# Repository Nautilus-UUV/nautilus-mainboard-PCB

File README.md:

# Nautilus Mainboard PCB
## Overview
This PCB houses an [STM32H7B0RBT6](https://www.st.com/resource/en/datasheet/stm32h7b0ab.pdf) together with a [CM4](https://pip-assets.raspberrypi.com/categories/634-raspberry-pi-compute-module-4/documents/RP-008168-DS-1-cm4-datasheet.pdf?disposition=inline). The STM32 is primarily used for communication over CanOpen with all the other PCBs while the CM4 is intended to run higher level calculations and then being shut off again. The CM4 is connected to an SSD. The CM4 and STM are connected over Uart (RX, TX) closely for communication and there is an integrated option for the STM to power off and on the CM4. (Currently the CM4's RUN_PG is connected to the STM32's pin number 10.) The STM has a crystal while the CM4 currently does not have one since it was not requested.

Additionally the mainboard provides two IMUs ([BMI088](https://www.bosch-sensortec.com/media/boschsensortec/downloads/datasheets/bst-bmi088-ds001.pdf)) that can be accessed over SPI on the STM32.

The Power supply is primarily provided by the UUV's battery lines (5V, 3.3V and GND) but the board also accepts USB-C 2.0 for both data and power inputs (only powering the CM4 and nothing else) or the 3.3V Power supply over the STM programmer pins. (only powers the STM32) The power logic is achieved using three [TPS2121RUXT](https://www.ti.com/lit/ds/symlink/tps2120.pdf?ts=1761678178328) (one for 5V, one for 3.3V and one for the GPIO reference of both microcontrollers.)

> [!CAUTION]
> The Power supply logic can be bypassed completely by soldering on 0 Ohm resistors on the designated spots for both 5V and 3.3V, but this still needs to be worked on.
> Also Im not 100% sure if the 0.8A provided by a laptop is sufficient for the CM4, it is possible that a direct battery connection is needed when programming it on the mainboard. For convenience please use the IO board for coding.

### WIP

Differential pairs have been routed and matched in length but the trace widths still need to be recalculated and adjusted.

The whole board works on 2 layers with an additional ground layer in mind (until now 1 free layer)

If someone wants to write a better README, feel free to do so, I'd appreciate it.

This PCB has not yet been reviewed or tested in a physical form.

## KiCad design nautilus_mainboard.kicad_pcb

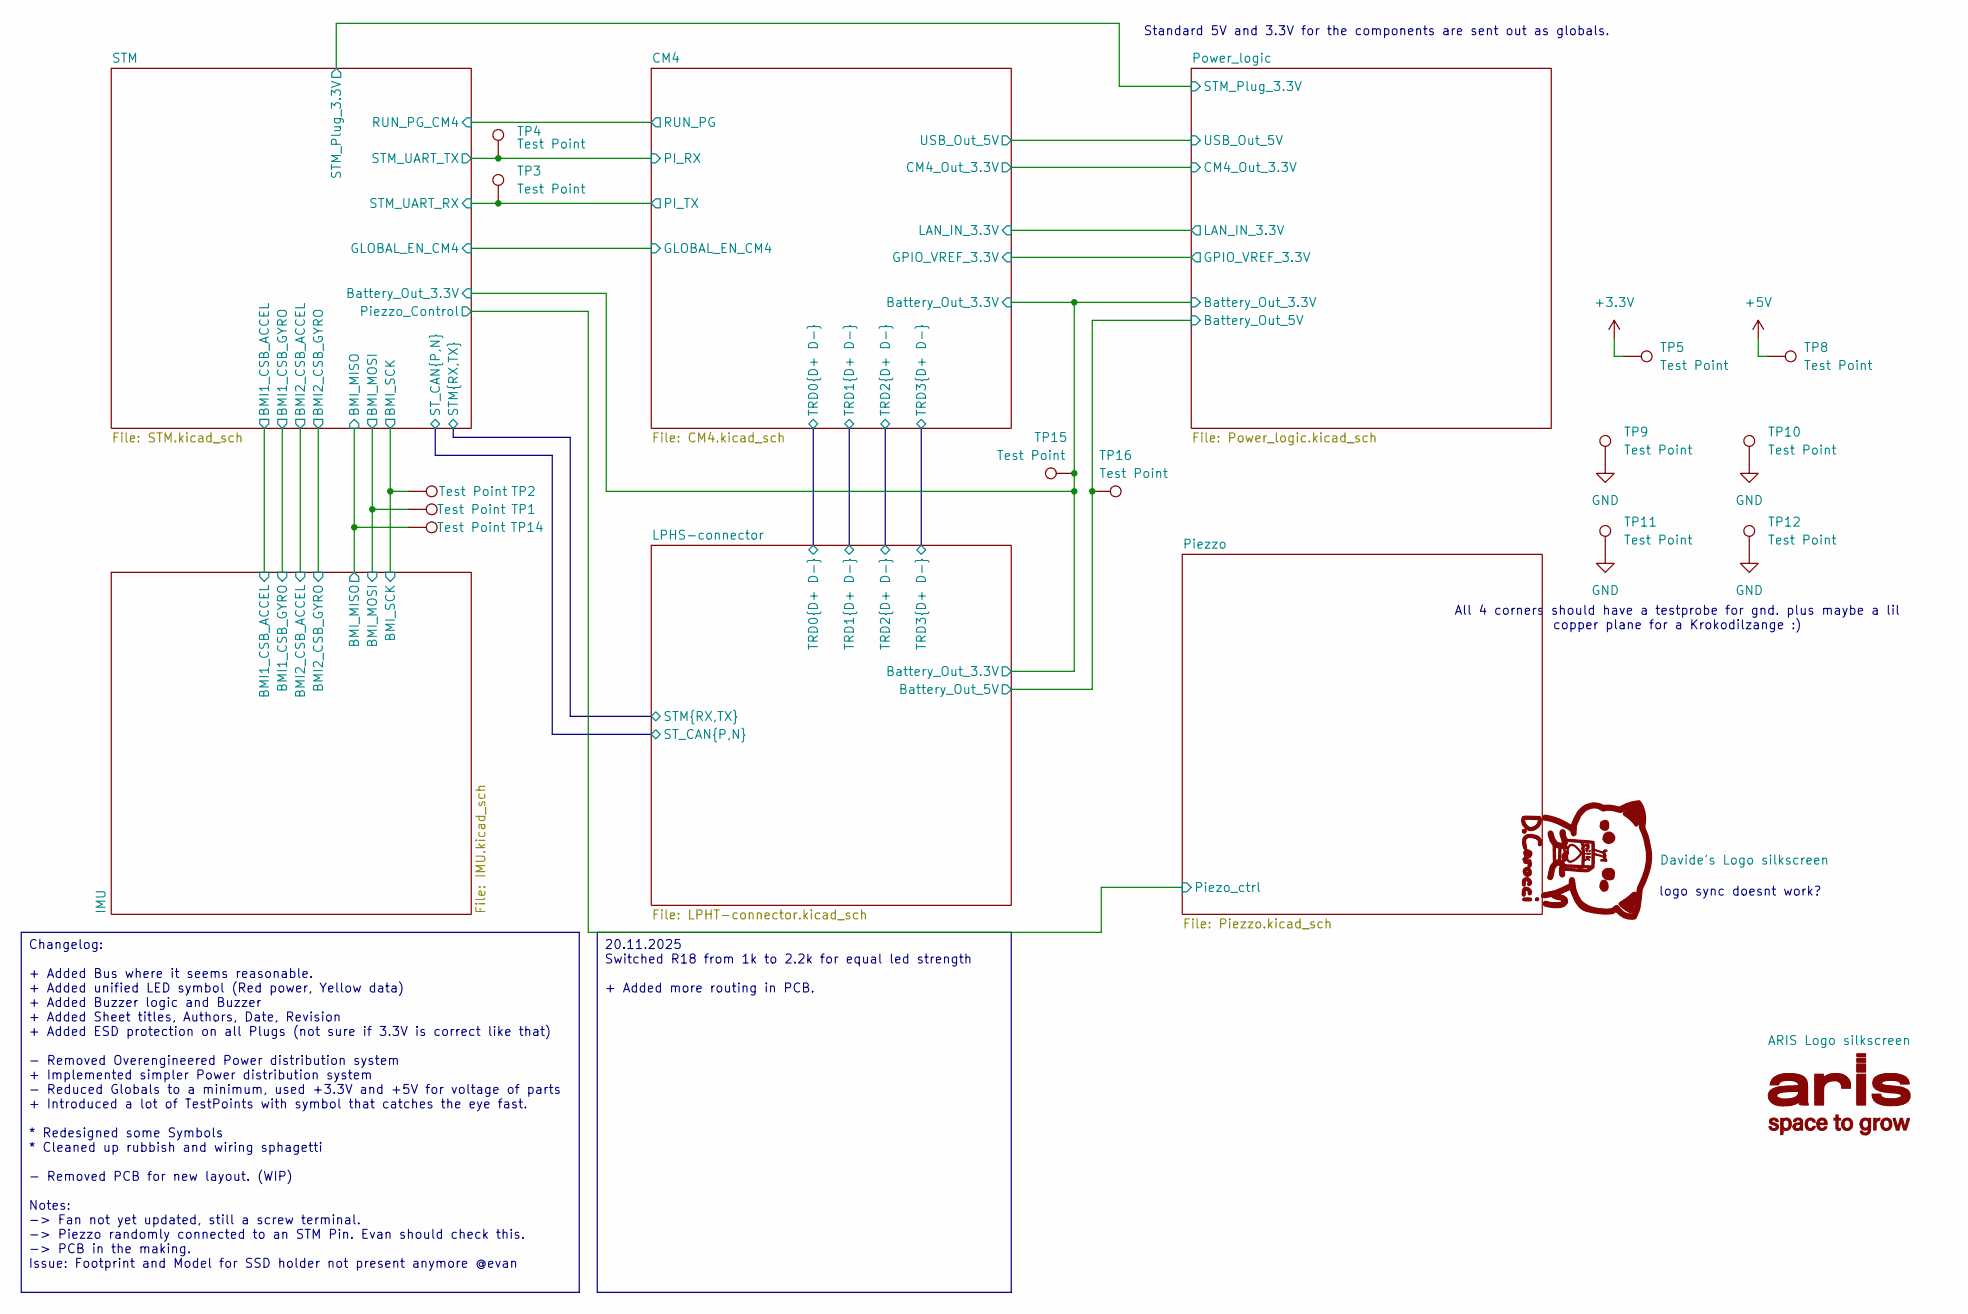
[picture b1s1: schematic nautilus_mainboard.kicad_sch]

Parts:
TP1, TP2, TP3, TP4, TP5, TP8, TP9, TP10, TP11, TP12, TP14, TP15, TP16: Test Point; TestPoint_Pad_D1.5mm

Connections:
+3.3V: TP5.1; also elsewhere on the board
+5V: TP8.1; also elsewhere on the board
/CM4/Battery_Out_3.3V: TP15.1; also elsewhere on the board
/IMU/BMI_MISO: TP14.1; also elsewhere on the board
/IMU/BMI_MOSI: TP1.1; also elsewhere on the board
/IMU/BMI_SCK: TP2.1; also elsewhere on the board
/LPHS-connector/Battery_Out_5V: TP16.1; also elsewhere on the board
/STM/PinoutSTM/USART2_RX: TP3.1; also elsewhere on the board
/STM/PinoutSTM/USART2_TX: TP4.1; also elsewhere on the board
GND: TP9.1, TP10.1, TP11.1, TP12.1; also elsewhere on the board

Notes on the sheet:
Standard 5V and 3.3V for the components are sent out as globals.
All 4 corners should have a testprobe for gnd. plus maybe a lil copper plane for a Krokodilzange :)
logo sync doesnt work?
20.11.2025 Switched R18 from 1k to 2.2k for equal led strength + Added more routing in PCB.
Changelog: + Added Bus where it seems reasonable. + Added unified LED symbol (Red power, Yellow data) + Added Buzzer logic and Buzzer + Added Sheet titles, Authors, Date, Revision + Added ESD protection on all Plugs (not sure if 3.3V is correct like that) - Removed Overengineered Power distribution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

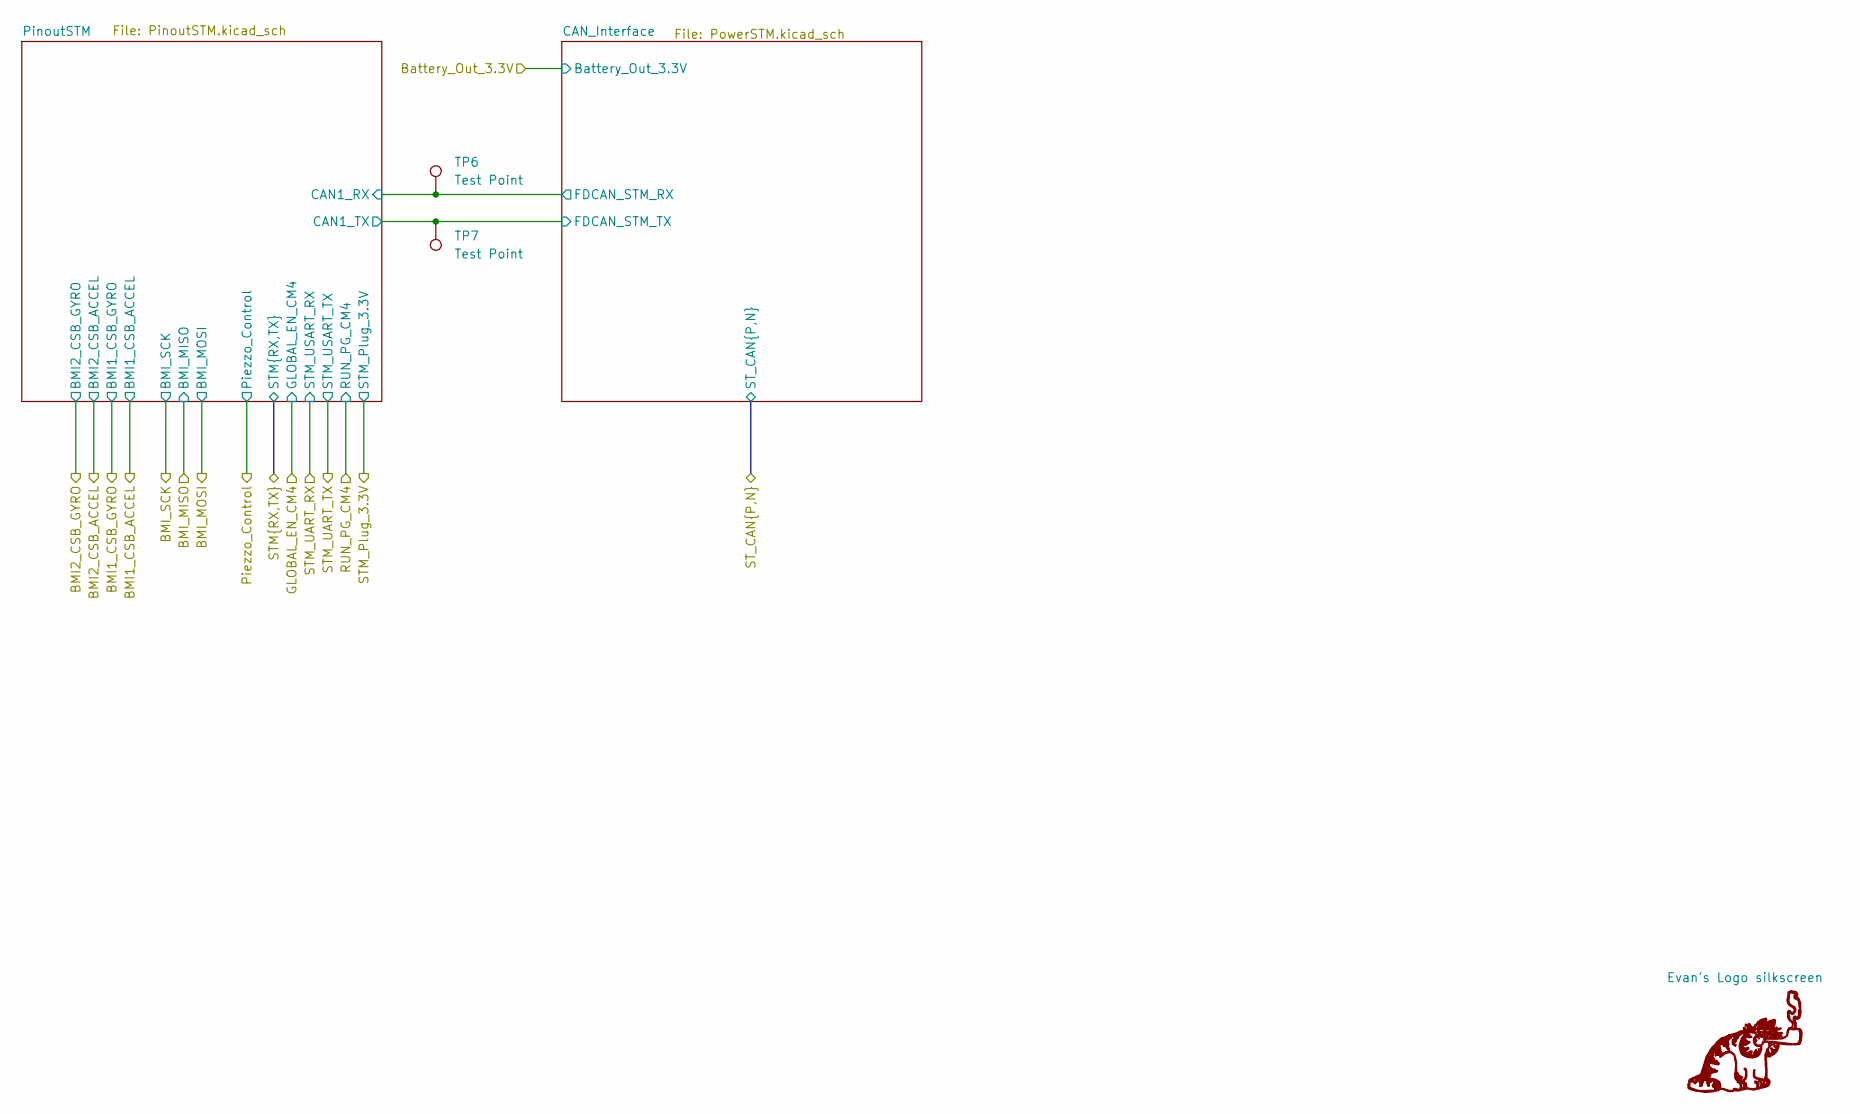
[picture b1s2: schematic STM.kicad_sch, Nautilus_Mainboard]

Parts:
TP6, TP7: Test Point; TestPoint_Pad_D1.5mm

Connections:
/STM/PinoutSTM/CAN1_RX: TP6.1; also elsewhere on the board
/STM/PinoutSTM/CAN1_TX: TP7.1; also elsewhere on the board

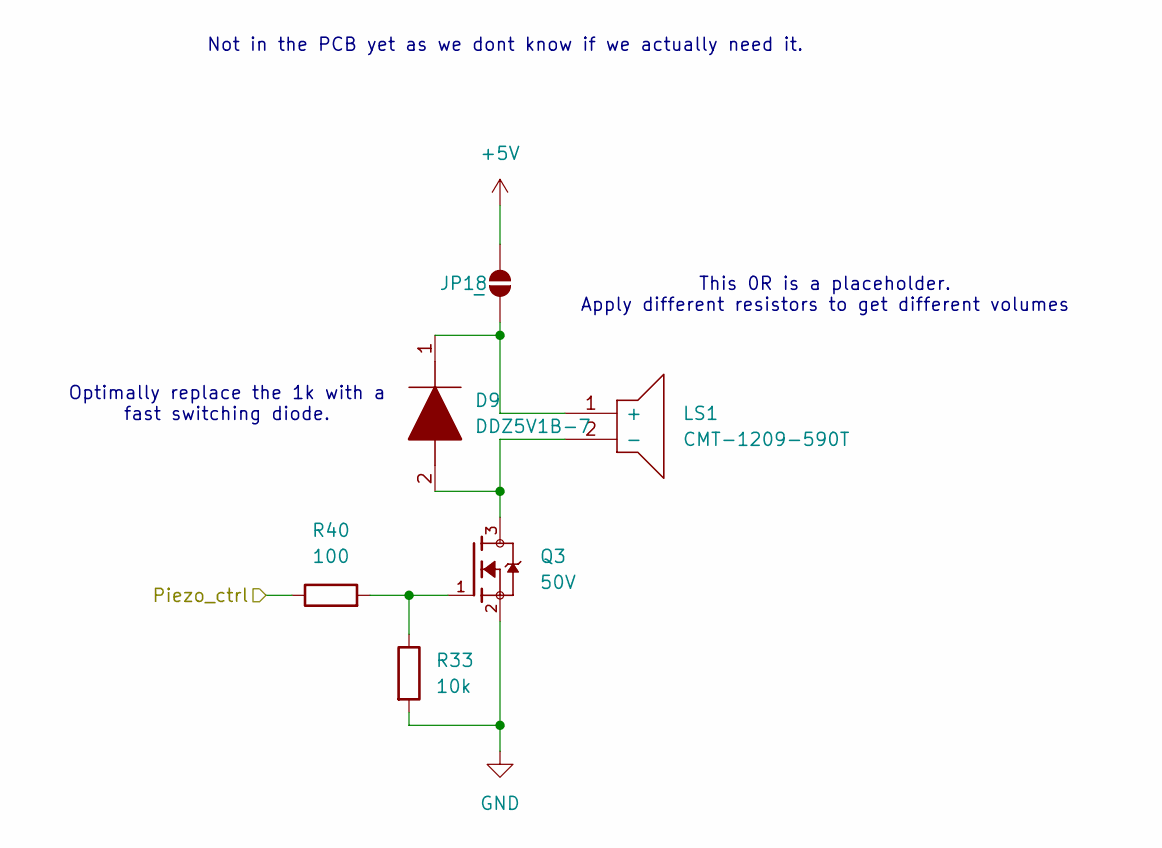
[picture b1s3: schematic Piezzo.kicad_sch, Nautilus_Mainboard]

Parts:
D9: DDZ5V1B-7; SOD3716X145N; Mouser Part Number 621-DDZ5V1B-7
JP18: -; SolderJumper-2_P1.3mm_Open_RoundedPad1.0x1.5mm
LS1: Piezo Buzzers & Audio Indicators 12mmx9mm deep Ma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; CMT1209590T; Mouser Part Number 179-CMT-1209-590T
Q3: 50V; onsemi_Mosfet_BSS138; PARTREV 30 Jan 2018
R33: 10k; R_0603_1608Metric; Tolerance 1 %; MPN 560112116005; LCSC CXXXXX
R40: 100; R_0402_1005Metric; Tolerance 1%; MPN ERJ-2RKF1000X; LCSC C413063

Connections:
+5V: JP18.2 (B); also elsewhere on the board
/Piezzo/Piezo_ctrl: R40.1; also elsewhere on the board
GND: Q3.2, R33.2; also elsewhere on the board
unnamed: D9.1, JP18.1 (A), LS1.1 (+)
unnamed: D9.2, LS1.2 (-), Q3.3
unnamed: Q3.1, R33.1, R40.2

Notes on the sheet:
Optimally replace the 1k with a fast switching diode.
This 0R is a placeholder. Apply different resistors to get different volumes
Not in the PCB yet as we dont know if we actually need it.

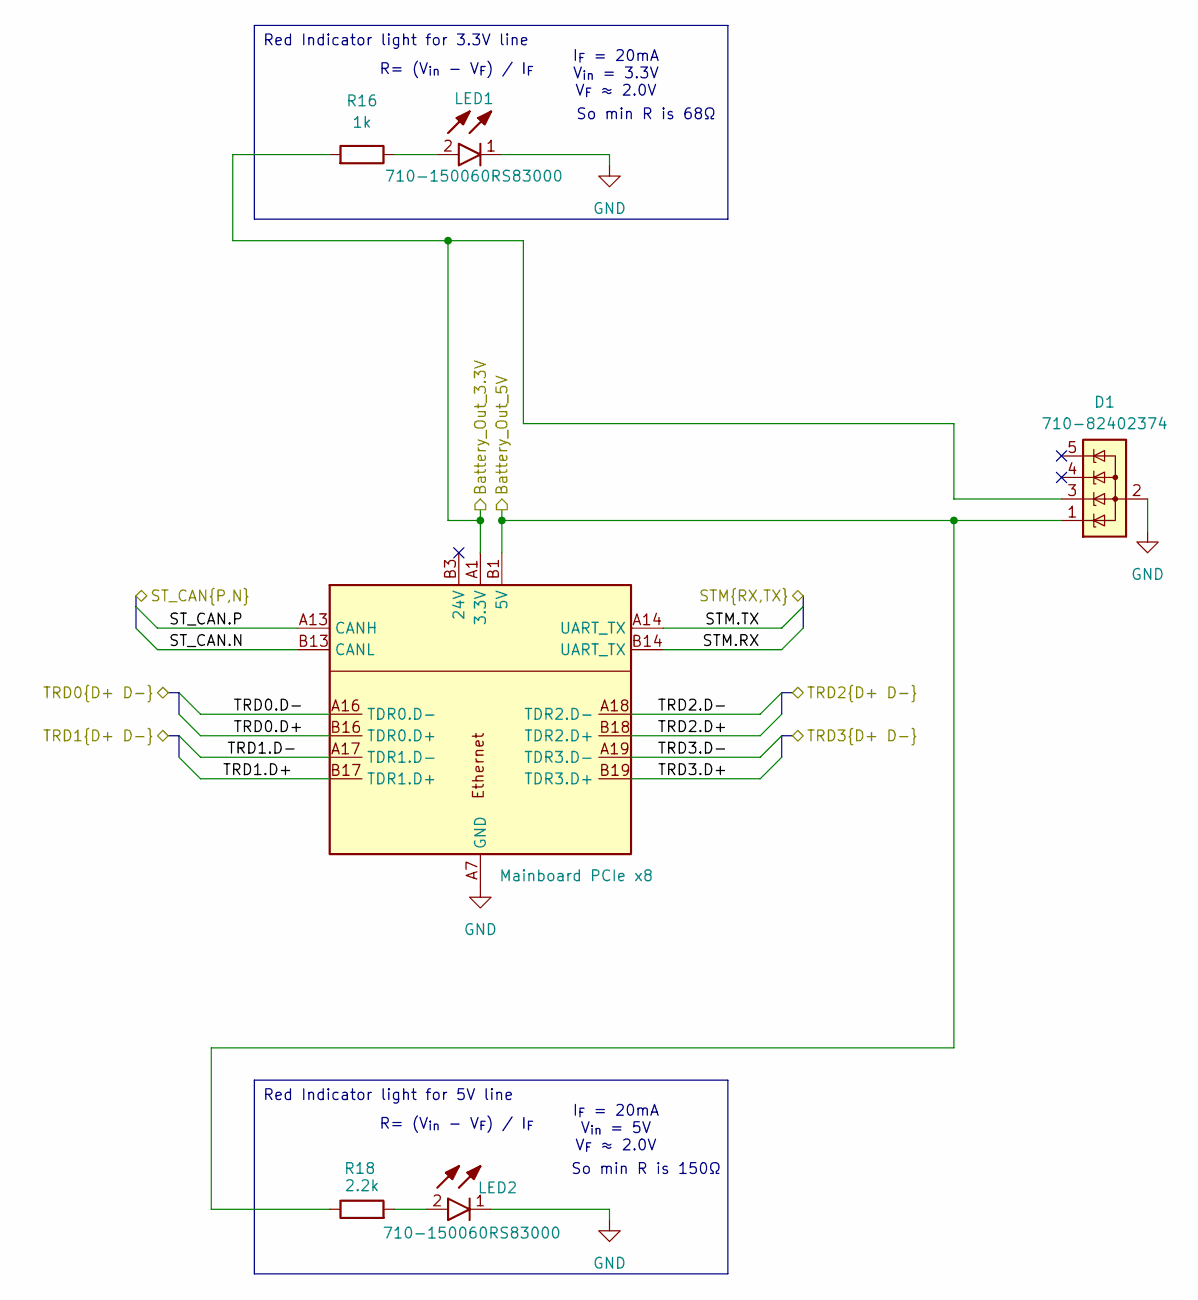
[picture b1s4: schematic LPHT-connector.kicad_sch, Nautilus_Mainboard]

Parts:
D1: 710-82402374; SOT-23-5; MPN 710-82402374
J2: Mainboard PCIe x8; BUS_PCIexpress_x8
LED1, LED2: 710-150060RS83000; Wuerth_LED_150060RS83000; Manufacturer_Part_Number 150060RS83000
R16: 1k; R_0603_1608Metric; Tolerance 1 %; MPN 560112116014; LCSC CXXXXX
R18: 2.2k; R_0603_1608Metric; Tolerance 1 %; MPN 560112116098; LCSC CXXXXX

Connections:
24V: J2.A3 (24V), J2.A4 (24V), J2.A5 (24V), J2.A6 (24V), J2.B4 (24V), J2.B5 (24V), J2.B6 (24V)
/CM4/Battery_Out_3.3V: D1.3 (K), J2.A1 (3.3V), J2.A2 (3.3V), R16.2; also elsewhere on the board
/CM4/TRD0.D+: J2.B16 (TDR0.D+); also elsewhere on the board
/CM4/TRD0.D-: J2.A16 (TDR0.D-); also elsewhere on the board
/CM4/TRD1.D+: J2.B17 (TDR1.D+); also elsewhere on the board
/CM4/TRD1.D-: J2.A17 (TDR1.D-); also elsewhere on the board
/CM4/TRD2.D+: J2.B18 (TDR2.D+); also elsewhere on the board
/CM4/TRD2.D-: J2.A18 (TDR2.D-); also elsewhere on the board
/CM4/TRD3.D+: J2.B19 (TDR3.D+); also elsewhere on the board
/CM4/TRD3.D-: J2.A19 (TDR3.D-); also elsewhere on the board
/LPHS-connector/Battery_Out_5V: D1.1 (K), J2.B1 (5V), R18.1; also elsewhere on the board
/LPHS-connector/STM.RX: J2.B14 (UART_TX); also elsewhere on the board
/LPHS-connector/STM.TX: J2.A14 (UART_TX); also elsewhere on the board
/LPHS-connector/ST_CAN.N: J2.B13 (CANL); also elsewhere on the board
/LPHS-connector/ST_CAN.P: J2.A13 (CANH); also elsewhere on the board
GND: D1.2 (A), J2.A7 (GND), J2.A8 (GND), J2.A9 (GND), J2.A10 (GND), J2.A11 (GND), J2.A12 (GND), J2.A21 (GND), J2.A24 (GND), J2.A27 (GND), J2.A29 (GND), J2.B7 (GND), J2.B8 (GND), J2.B9 (GND), J2.B10 (GND), J2.B11 (GND), J2.B12 (GND), LED1.1 (K), LED2.1 (K); also elsewhere on the board
unnamed: LED1.2 (A), R16.1
unnamed: LED2.2 (A), R18.2

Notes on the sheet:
I_{F} = 20mA V_{in} = 5V V_{F} ≈ 2.0V
R= (V_{in} - V_{F}) / I_{F}
So min R is 150Ω
So min R is 68Ω
I_{F} = 20mA V_{in} = 3.3V V_{F} ≈ 2.0V
Red Indicator light for 3.3V line
Red Indicator light for 5V line

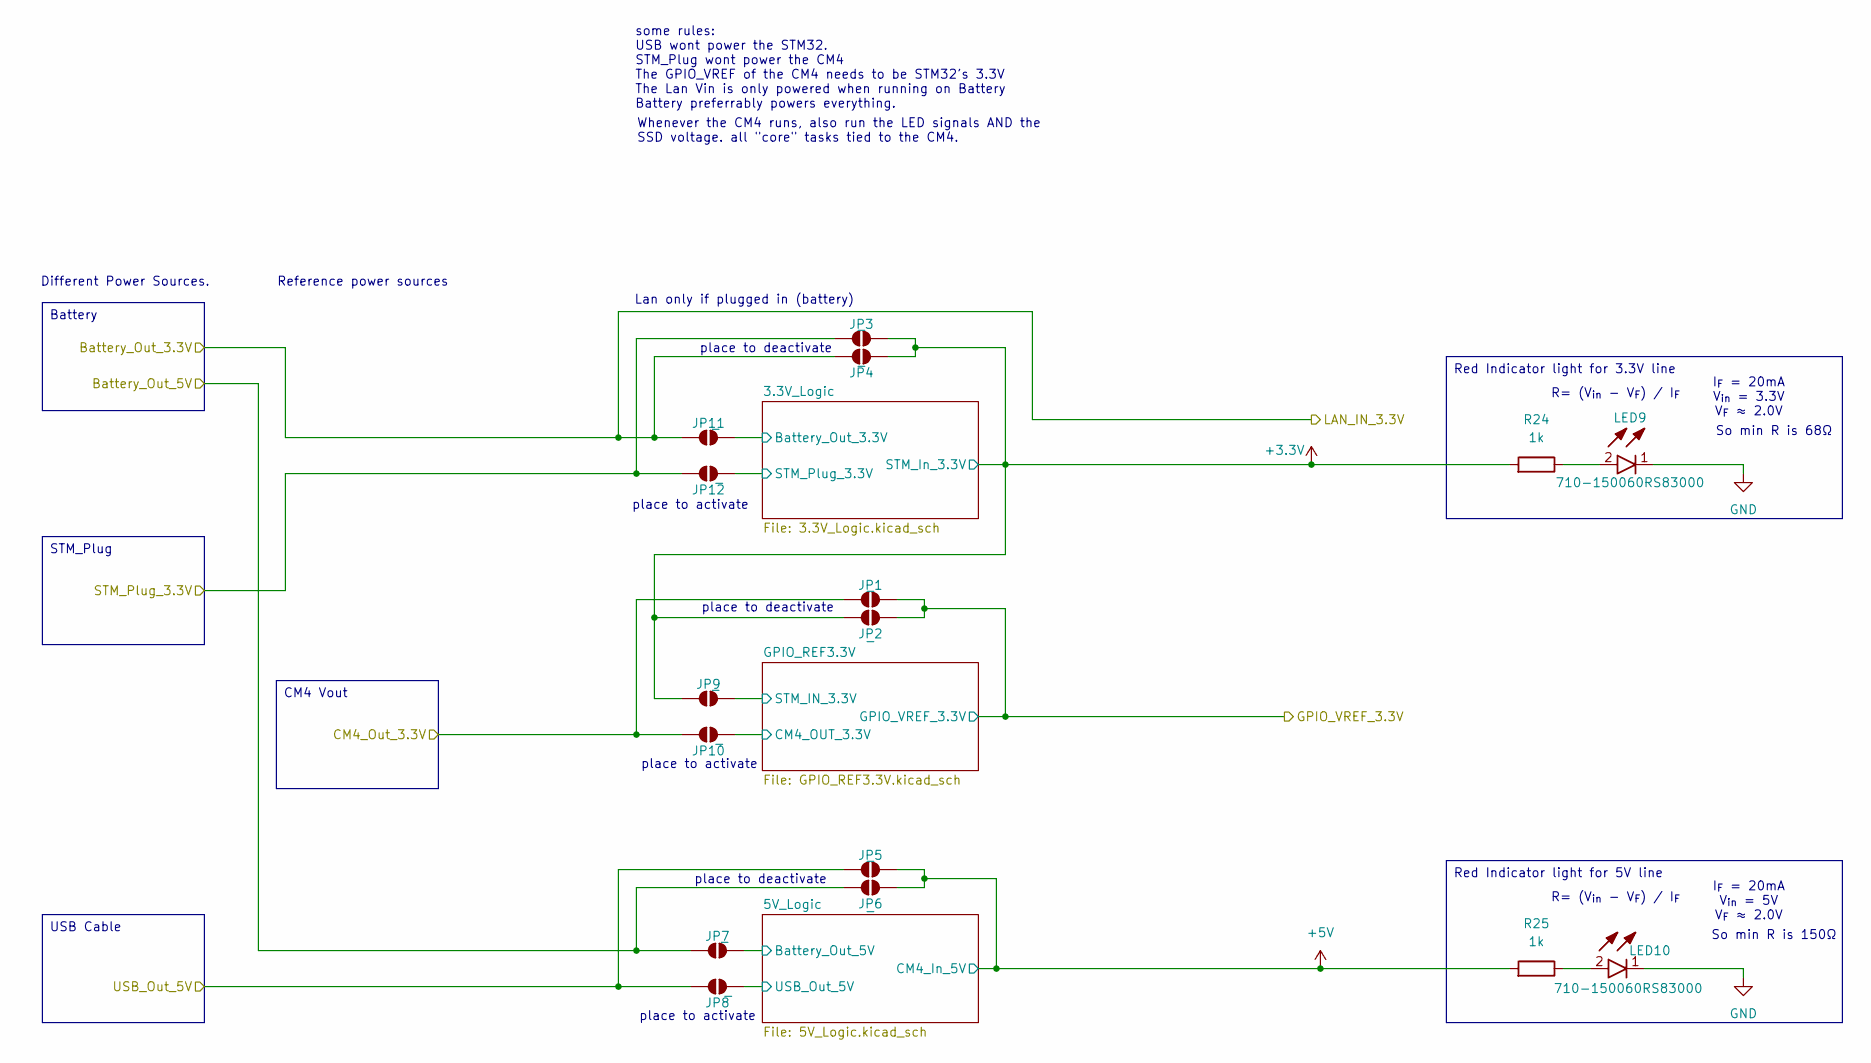
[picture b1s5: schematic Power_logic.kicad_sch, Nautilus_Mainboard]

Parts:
JP1, JP2, JP3, JP4, JP5, JP6, JP7, JP8, JP9, JP10, JP11, JP12: -; SolderJumper-2_P1.3mm_Open_RoundedPad1.0x1.5mm
LED9, LED10: 710-150060RS83000; Wuerth_LED_150060RS83000; Manufacturer_Part_Number 150060RS83000
R24, R25: 1k; R_0603_1608Metric; Tolerance 1 %; MPN 560112116014; LCSC CXXXXX

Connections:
+3.3V: JP2.1 (A), JP3.2 (B), JP4.2 (B), JP9.1 (A), R24.2; also elsewhere on the board
+5V: JP5.2 (B), JP6.2 (B), R25.2; also elsewhere on the board
/CM4/Battery_Out_3.3V: JP4.1 (A), JP11.1 (A); also elsewhere on the board
/CM4/CM4_Out_3.3V: JP1.1 (A), JP10.1 (A); also elsewhere on the board
/CM4/GPIO_VREF_3.3V: JP1.2 (B), JP2.2 (B); also elsewhere on the board
/CM4/USB_Out_5V: JP5.1 (A), JP8.1 (A); also elsewhere on the board
/LPHS-connector/Battery_Out_5V: JP6.1 (A), JP7.1 (A); also elsewhere on the board
/Power_logic/3.3V_Logic/Battery_Out_3.3V: JP11.2 (B); also elsewhere on the board
/Power_logic/3.3V_Logic/STM_Plug_3.3V: JP12.2 (B); also elsewhere on the board
/Power_logic/5V_Logic/Battery_Out_5V: JP7.2 (B); also elsewhere on the board
/Power_logic/5V_Logic/USB_Out_5V: JP8.2 (B); also elsewhere on the board
/Power_logic/GPIO_REF3.3V/CM4_OUT_3.3V: JP10.2 (B); also elsewhere on the board
/Power_logic/GPIO_REF3.3V/STM_IN_3.3V: JP9.2 (B); also elsewhere on the board
/Power_logic/STM_Plug_3.3V: JP3.1 (A), JP12.1 (A); also elsewhere on the board
GND: LED9.1 (K), LED10.1 (K); also elsewhere on the board
unnamed: LED9.2 (A), R24.1
unnamed: LED10.2 (A), R25.1

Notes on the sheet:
place to activate
Whenever the CM4 runs, also run the LED signals AND the SSD voltage. all "core" tasks tied to the CM4.
I_{F} = 20mA V_{in} = 3.3V V_{F} ≈ 2.0V
Different Power Sources.
R= (V_{in} - V_{F}) / I_{F}
some rules: USB wont power the STM32. STM_Plug wont power the CM4 The GPIO_VREF of the CM4 needs to be STM32's 3.3V The Lan Vin is only powered when running on Battery Battery preferrably powers everything.
place to deactivate
So min R is 150Ω
Lan only if plugged in (battery)
I_{F} = 20mA V_{in} = 5V V_{F} ≈ 2.0V
Reference power sources
So min R is 68Ω
CM4 Vout
Red Indicator light for 5V line
USB Cable
Battery
STM_Plug
Red Indicator light for 3.3V line

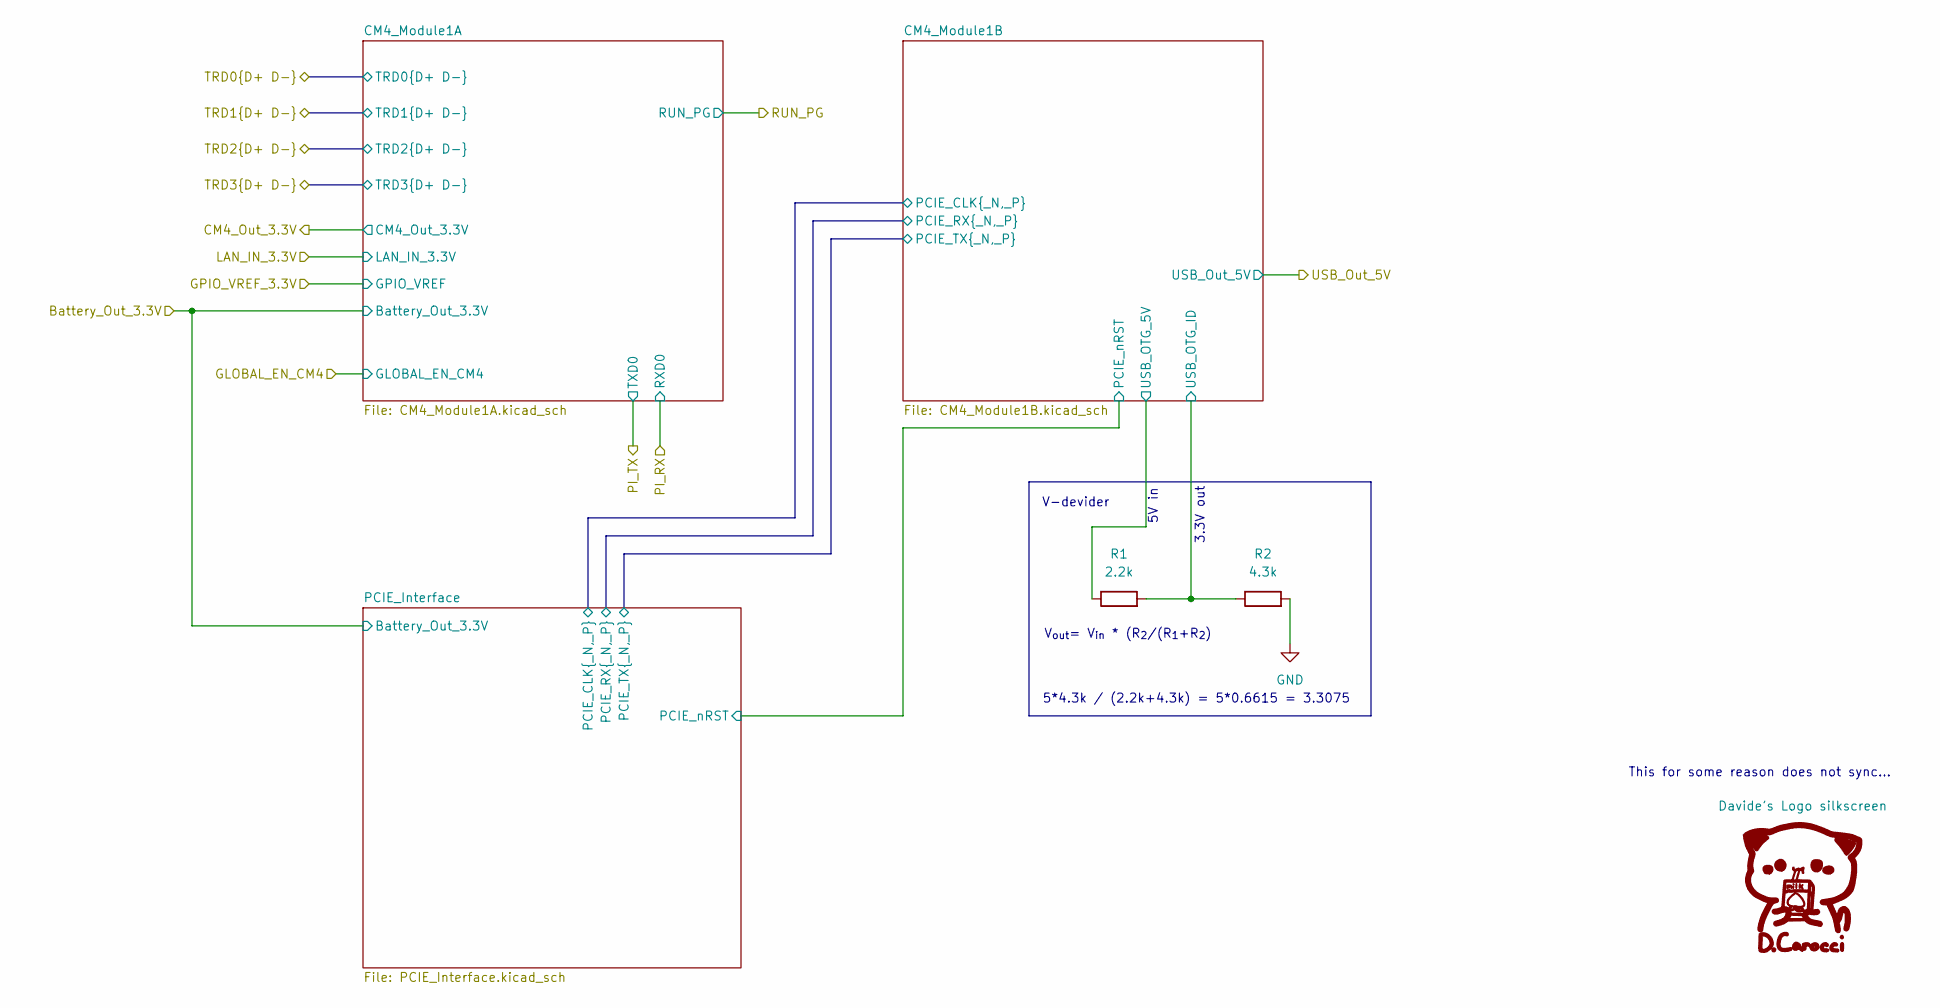
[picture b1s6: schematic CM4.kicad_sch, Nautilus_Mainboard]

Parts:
R1: 2.2k; R_0603_1608Metric; Tolerance 1 %; MPN 560112116098; LCSC CXXXXX
R2: 4.3k; R_0603_1608Metric; Tolerance 1 %; MPN 560112116141; LCSC CXXXXX

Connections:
/CM4/CM4_Module1B/USB_OTG_ID: R1.2, R2.1; also elsewhere on the board
/CM4/USB_Out_5V: R1.1; also elsewhere on the board
GND: R2.2; also elsewhere on the board

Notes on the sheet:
This for some reason does not sync...
5V in
V-devider
5*4.3k / (2.2k+4.3k) = 5*0.6615 = 3.3075
3.3V out
V_{out}= V_{in} * (R_{2}/(R_{1}+R_{2})

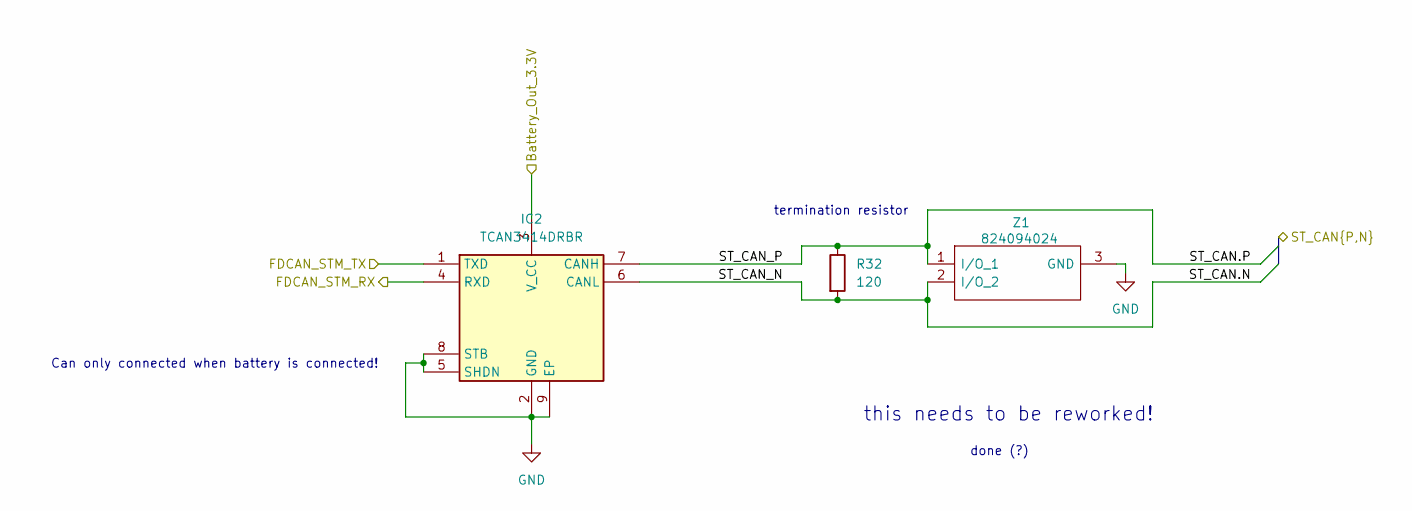
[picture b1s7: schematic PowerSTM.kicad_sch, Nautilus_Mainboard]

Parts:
IC2: TCAN3414DRBR; Mouser Part Number 595-TCAN3414DRBR
R32: 120; R_0603_1608Metric; Tolerance 1%; MPN 560112116119; LCSC CXXXXX
Z1: 824094024; SOT95P240X104-3N; Mouser Part Number 710-824094024

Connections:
/CM4/Battery_Out_3.3V: IC2.3 (V_CC); also elsewhere on the board
/LPHS-connector/ST_CAN.N: IC2.6 (CANL), R32.2, Z1.2 (I/O_2); also elsewhere on the board
/LPHS-connector/ST_CAN.P: IC2.7 (CANH), R32.1, Z1.1 (I/O_1); also elsewhere on the board
/STM/PinoutSTM/CAN1_RX: IC2.4 (RXD); also elsewhere on the board
/STM/PinoutSTM/CAN1_TX: IC2.1 (TXD); also elsewhere on the board
GND: IC2.2 (GND), IC2.5 (SHDN), IC2.8 (STB), IC2.9 (EP), Z1.3 (GND); also elsewhere on the board

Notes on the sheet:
Can only connected when battery is connected!
done (?)
termination resistor
this needs to be reworked!

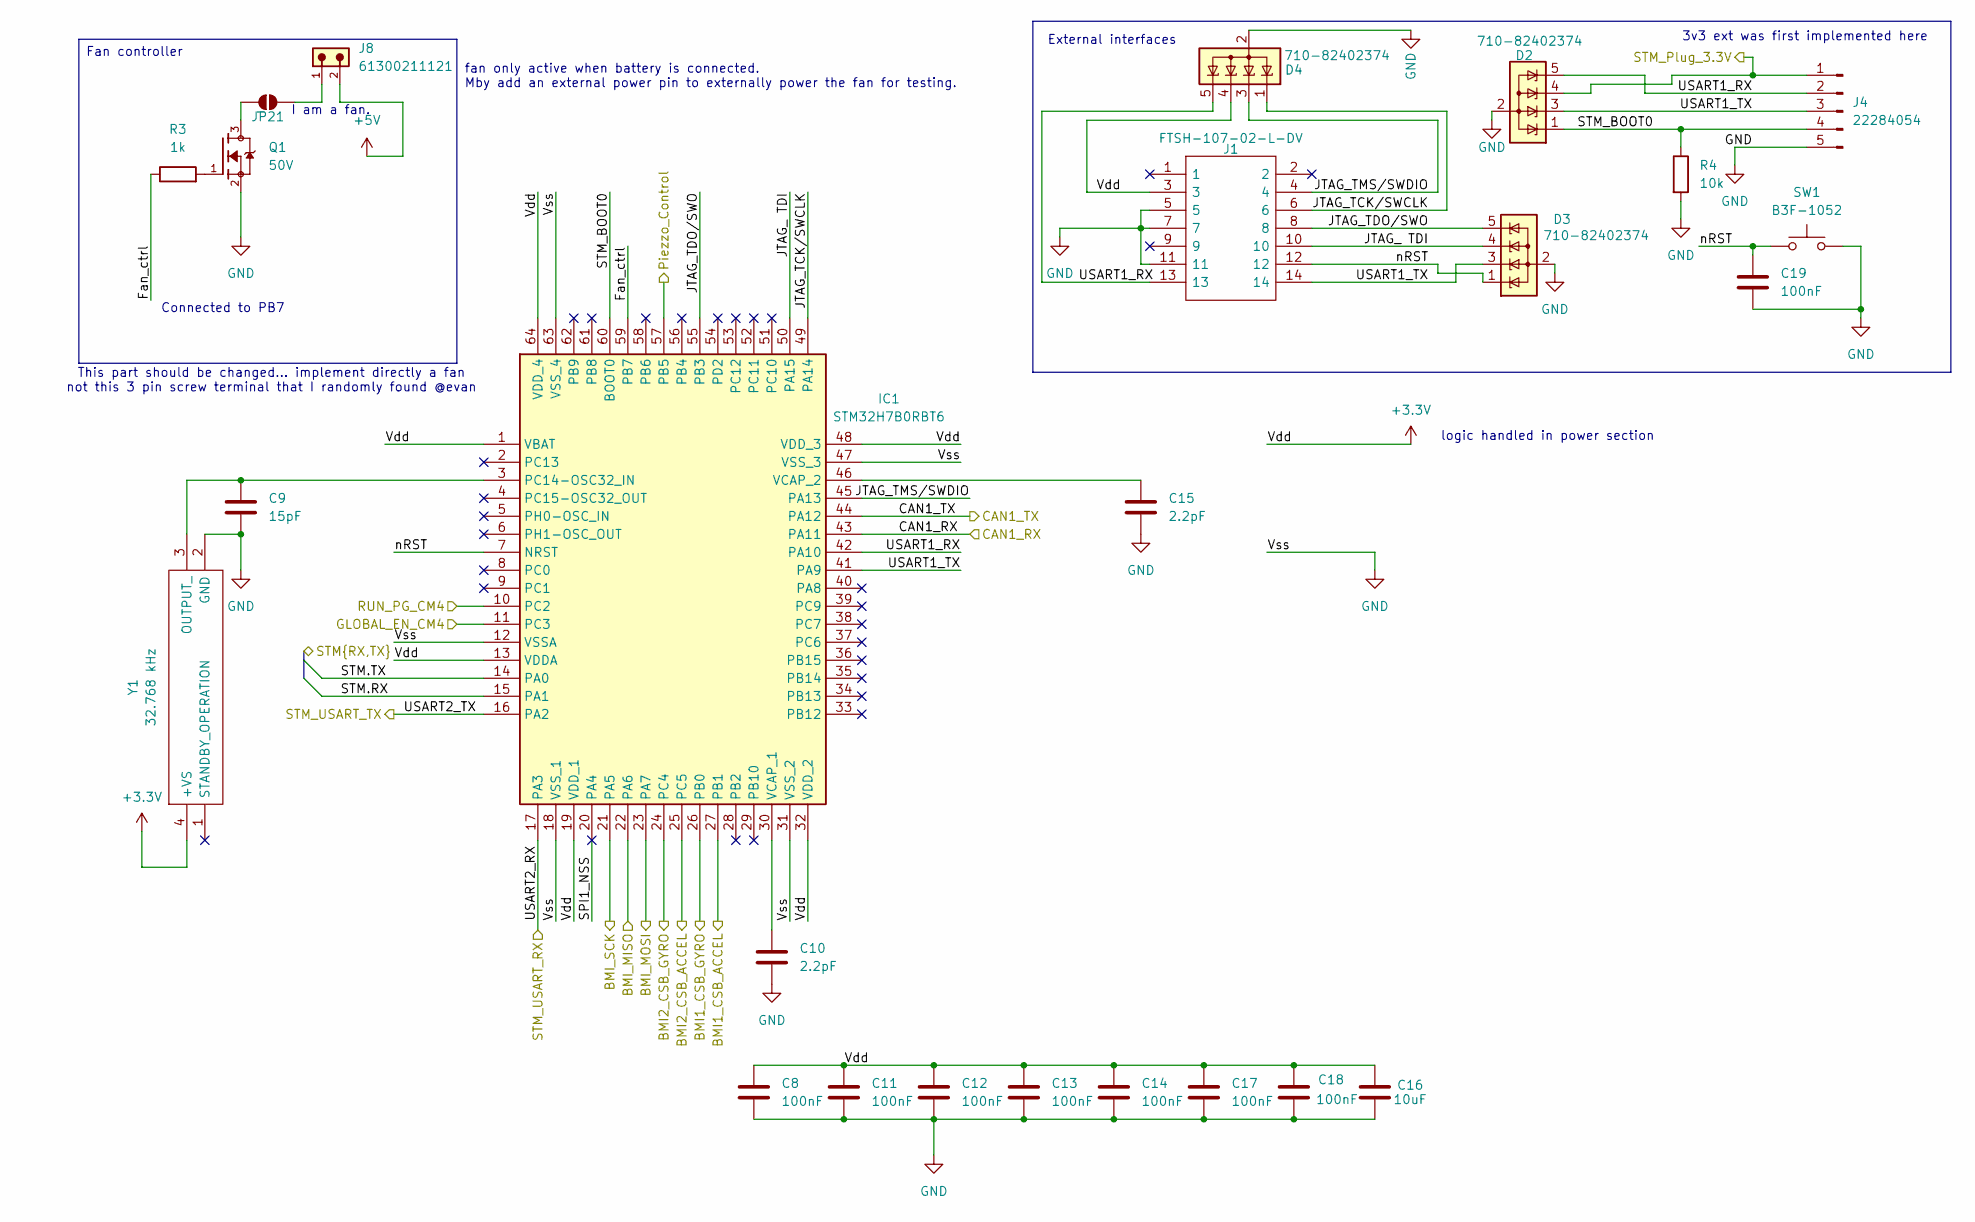
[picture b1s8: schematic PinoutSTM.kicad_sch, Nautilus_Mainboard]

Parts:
C8, C11, C12, C13, C14, C17, C18, C19: 100nF; C_0603_1608Metric; Voltage 50V; Tolerance 10%; MPN 885012206095; LCSC CXXXXX
C9: 15pF; C_0603_1608Metric; Voltage 50V; Tolerance 5%; MPN 885012006052; LCSC CXXXXX
C10, C15: 2.2pF; C_0603_1608Metric; Voltage 50V; Tolerance ±0.5pF; MPN 885012006047; LCSC CXXXXX
C16: 10uF; C_1210_3225Metric; Voltage 100V; Tolerance 10%; MPN GRM32EC72A106KE05; LCSC C5444485
D2, D3, D4: 710-82402374; SOT-23-5; MPN 710-82402374
IC1: STM32H7B0RBT6; LQFP-64_10x10mm_P0.5mm; Voltage 1.62V - 3.6V; Mouser Part Number 511-STM32H7B0RBT6
J1: FTSH-107-02-L-DV; FTSH-107-XX-YYY-DV; Mouser Part Number 200-FTSH10702LDV
J4: Header male 1x05; PinHeader_1x05_P2.54mm_Vertical; MPN 22284054; LCSC C7501263
J8: 61300211121; Wurth_Con_61300211121; MPN 61300211121
JP21: -; SolderJumper-2_P1.3mm_Open_RoundedPad1.0x1.5mm
Q1: 50V; onsemi_Mosfet_BSS138; PARTREV 30 Jan 2018
R3: 1k; R_0603_1608Metric; Tolerance 1 %; MPN 560112116014; LCSC CXXXXX
R4: 10k; R_0603_1608Metric; Tolerance 1 %; MPN 560112116005; LCSC CXXXXX
SW1: Button Switch SPST-No; SW_PUSH_6mm; MPN B3F-1052; LCSC C87037
Y1: 32.768 kHz; 830205028309; Mouser Part Number 710-830205028309

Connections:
+3.3V: C8.1, C11.1, C12.1, C13.1, C14.1, C16.1, C17.1, C18.1, D4.4 (K), IC1.1 (VBAT), IC1.13 (VDDA), IC1.19 (VDD_1), IC1.32 (VDD_2), IC1.48 (VDD_3), IC1.64 (VDD_4), J1.3, Y1.4 (+VS); also elsewhere on the board
+5V: J8.2; also elsewhere on the board
/CM4/GLOBAL_EN_CM4: IC1.11 (PC3); also elsewhere on the board
/CM4/RUN_PG: IC1.10 (PC2); also elsewhere on the board
/IMU/BMI1_CSB_ACCEL: IC1.27 (PB1); also elsewhere on the board
/IMU/BMI1_CSB_GYRO: IC1.26 (PB0); also elsewhere on the board
/IMU/BMI2_CSB_ACCEL: IC1.25 (PC5); also elsewhere on the board
/IMU/BMI2_CSB_GYRO: IC1.24 (PC4); also elsewhere on the board
/IMU/BMI_MISO: IC1.22 (PA6); also elsewhere on the board
/IMU/BMI_MOSI: IC1.23 (PA7); also elsewhere on the board
/IMU/BMI_SCK: IC1.21 (PA5); also elsewhere on the board
/LPHS-connector/STM.RX: IC1.15 (PA1); also elsewhere on the board
/LPHS-connector/STM.TX: IC1.14 (PA0); also elsewhere on the board
/Piezzo/Piezo_ctrl: IC1.57 (PB5); also elsewhere on the board
/Power_logic/STM_Plug_3.3V: D2.4 (K), J4.1; also elsewhere on the board
/STM/PinoutSTM/CAN1_RX: IC1.43 (PA11); also elsewhere on the board
/STM/PinoutSTM/CAN1_TX: IC1.44 (PA12); also elsewhere on the board
/STM/PinoutSTM/Fan_ctrl: IC1.59 (PB7), R3.1
/STM/PinoutSTM/JTAG_ TDI: D3.4 (K), IC1.50 (PA15), J1.10
/STM/PinoutSTM/JTAG_TCK/SWCLK: D4.1 (K), IC1.49 (PA14), J1.6
/STM/PinoutSTM/JTAG_TDO/SWO: D3.5 (K), IC1.55 (PB3), J1.8
/STM/PinoutSTM/JTAG_TMS/SWDIO: D4.3 (K), IC1.45 (PA13), J1.4
/STM/PinoutSTM/SPI1_NSS: IC1.20 (PA4)
/STM/PinoutSTM/STM_BOOT0: D2.1 (K), IC1.60 (BOOT0), J4.4, R4.1
/STM/PinoutSTM/USART1_RX: D2.5 (K), D4.5 (K), IC1.42 (PA10), J1.13, J4.2
/STM/PinoutSTM/USART1_TX: D2.3 (K), D3.3 (K), IC1.41 (PA9), J1.14, J4.3
/STM/PinoutSTM/USART2_RX: IC1.17 (PA3); also elsewhere on the board
/STM/PinoutSTM/USART2_TX: IC1.16 (PA2); also elsewhere on the board
/STM/PinoutSTM/nRST: C19.1, D3.1 (K), IC1.7 (NRST), J1.12, SW1.1
GND: C8.2, C9.2, C10.2, C11.2, C12.2, C13.2, C14.2, C15.2, C16.2, C17.2, C18.2, C19.2, D2.2 (A), D3.2 (A), D4.2 (A), IC1.12 (VSSA), IC1.18 (VSS_1), IC1.31 (VSS_2), IC1.47 (VSS_3), IC1.63 (VSS_4), J1.5, J1.7, J1.11, J4.5, Q1.2, R4.2, SW1.2, Y1.2 (GND); also elsewhere on the board
unnamed: C9.1, IC1.3 (PC14-OSC32_IN), Y1.3 (OUTPUT_)
unnamed: C10.1, IC1.30 (VCAP_1)
unnamed: C15.1, IC1.46 (VCAP_2)
unnamed: J8.1, JP21.1 (A)
unnamed: JP21.2 (B), Q1.3
unnamed: Q1.1, R3.2

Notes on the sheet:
I am a fan.
Connected to PB7
fan only active when battery is connected. Mby add an external power pin to externally power the fan for testing.
logic handled in power section
External interfaces
3v3 ext was first implemented here
This part should be changed... implement directly a fan not this 3 pin screw terminal that I randomly found @evan
Fan controller

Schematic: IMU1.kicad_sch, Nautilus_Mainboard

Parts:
C28, C29: 100nF; C_0603_1608Metric; Voltage 50V; Tolerance 10%; MPN 885012206095; LCSC CXXXXX
JP19: -; SolderJumper-2_P1.3mm_Open_RoundedPad1.0x1.5mm
U2: 262-BMI088; Bosch_IMU_BMI088; MPN 262-BMI088

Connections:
+3.3V: JP19.2 (B); also elsewhere on the board
/IMU/BMI2_CSB_ACCEL: U2.14 (CSB1); also elsewhere on the board
/IMU/BMI2_CSB_GYRO: U2.5 (CSB2); also elsewhere on the board
/IMU/BMI_MISO: U2.10 (SDO2), U2.15 (SDO1); also elsewhere on the board
/IMU/BMI_MOSI: U2.9 (SDA/SDI); also elsewhere on the board
/IMU/BMI_SCK: U2.8 (SCL/SCK); also elsewhere on the board
/IMU/IMU2/VDD: C28.1, C29.1, JP19.1 (A), U2.3 (VDD), U2.11 (VDDIO)
GND: C28.2, C29.2, U2.2 (NC), U2.4 (GNDA), U2.6 (GNDIO), U2.7 (PS); also elsewhere on the board

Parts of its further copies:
C43, C44: 100nF; C_0603_1608Metric; Voltage 50V; Tolerance 10%; MPN 885012206095; LCSC CXXXXX
JP20: -; SolderJumper-2_P1.3mm_Open_RoundedPad1.0x1.5mm
U1: 262-BMI088; Bosch_IMU_BMI088; MPN 262-BMI088

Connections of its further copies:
+3.3V: JP20.2 (B); also elsewhere on the board
/IMU/BMI1_CSB_ACCEL: U1.14 (CSB1); also elsewhere on the board
/IMU/BMI1_CSB_GYRO: U1.5 (CSB2); also elsewhere on the board
/IMU/BMI_MISO: U1.10 (SDO2), U1.15 (SDO1); also elsewhere on the board
/IMU/BMI_MOSI: U1.9 (SDA/SDI); also elsewhere on the board
/IMU/BMI_SCK: U1.8 (SCL/SCK); also elsewhere on the board
/IMU/IMU1/VDD: C43.1, C44.1, JP20.1 (A), U1.3 (VDD), U1.11 (VDDIO)
GND: C43.2, C44.2, U1.2 (NC), U1.4 (GNDA), U1.6 (GNDIO), U1.7 (PS); also elsewhere on the board

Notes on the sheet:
Same voltage used for logic line
Those are for interrupts.
Kill power
